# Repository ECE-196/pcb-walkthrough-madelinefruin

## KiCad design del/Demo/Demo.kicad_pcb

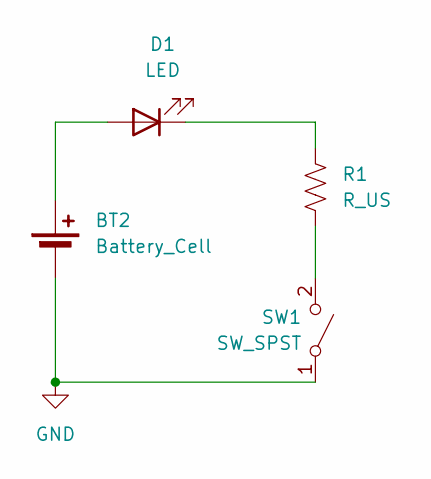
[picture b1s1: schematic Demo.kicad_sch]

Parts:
BT2: Battery_Cell; BatteryHolder_Keystone_103_1x20mm
D1: LED; LED_2512_6332Metric
R1: R_US; R_2512_6332Metric
SW1: SW_SPST; SW_PUSH_6mm_H4.3mm

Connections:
GND: BT2.2 (-), SW1.1 (A)
unnamed: BT2.1 (+), D1.2 (A)
unnamed: D1.1 (K), R1.1
unnamed: R1.2, SW1.2 (B)

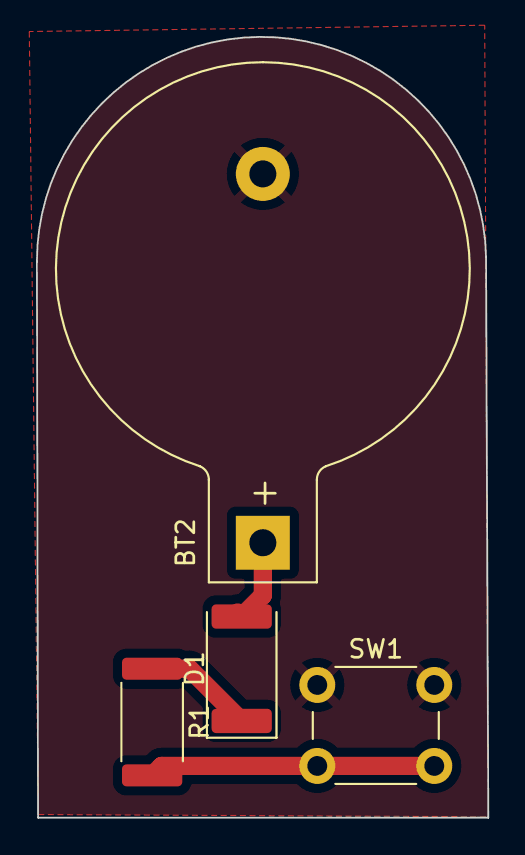
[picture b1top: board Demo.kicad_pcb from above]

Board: 2 copper layers, 25.1 x 43.4 mm, 4 parts (0 on the bottom side), 4 nets.

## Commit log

2024-10-07 add deadline
2024-10-08 All KiCad Things
    For some reason my kicad stuff ended up in a folder named del?
